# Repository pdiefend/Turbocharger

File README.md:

# Turbocharger
Turbocharger started as a Google Code Project and is in the process of being migrated to GitHub.
Farewell old friend.

The Turbocharger Arduino motor driver is a motor driver designed to amplify the abilities for Arduino robot control. This driver board includes encoder counters, an on-board motor driver, and serial communication headers to be as adaptable as possible for projects needing small motors with encoders.

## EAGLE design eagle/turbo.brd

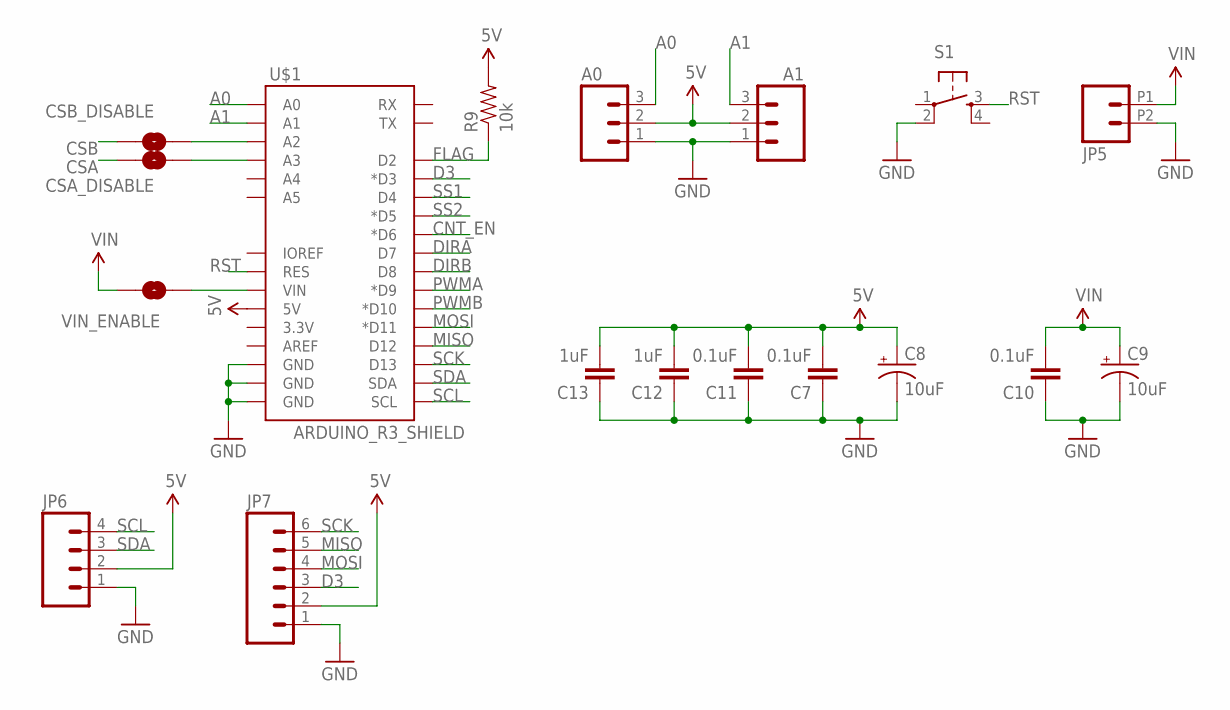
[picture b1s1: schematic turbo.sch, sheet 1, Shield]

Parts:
A0, A1: M03LOCK; 1X03_LOCK
C7, C10, C11: 0.1uF; 0603-CAP
C8, C9: 10uF; PANASONIC_C
C12, C13: 1uF; 0603-CAP
CSA_DISABLE: SOLDERJUMPERTRACE; SJ_2S-TRACE
CSB_DISABLE: SOLDERJUMPERTRACE; SJ_2S-TRACE
JP5: M022.54MM_SCREWTERM; 1X02_2.54_SCREWTERM
JP6: M04POLAR_LOCK; MOLEX-1X4_LOCK
JP7: M06POLAR_LOCK; MOLEX-1X6_LOCK
R9: 10k; 0603-RES
S1: TAC_SWITCHSMD; TACTILE_SWITCH_SMD
U$1: ARDUINO_R3_SHIELD; UNO_R3_SHIELD
VIN_ENABLE: SOLDERJUMPERNO; SJ_2S-NO

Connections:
5V: A0.2, A1.2, C7.2, C8.+, C11.2, C12.2, C13.2, JP6.2, JP7.2, R9.2, U$1.5V; also elsewhere on the board
A0: A0.3, U$1.A0
A1: A1.3, U$1.A1
CNT_EN: U$1.D6 (*D6); also elsewhere on the board
CSA: CSA_DISABLE.2; also elsewhere on the board
CSB: CSB_DISABLE.2; also elsewhere on the board
D3: JP7.3, U$1.D3 (*D3)
DIRA: U$1.D7; also elsewhere on the board
DIRB: U$1.D8; also elsewhere on the board
FLAG: R9.1, U$1.D2; also elsewhere on the board
GND: A0.1, A1.1, C7.1, C8.-, C9.-, C10.1, C11.1, C12.1, C13.1, JP5.P2 (2), JP6.1, JP7.1, S1.2, U$1.GND@0 (GND), U$1.GND@1 (GND), U$1.GND@2 (GND); also elsewhere on the board
MISO: JP7.5, U$1.D12; also elsewhere on the board
MOSI: JP7.4, U$1.D11 (*D11); also elsewhere on the board
unnamed: CSB_DISABLE.1, U$1.A2
unnamed: CSA_DISABLE.1, U$1.A3
unnamed: U$1.VIN, VIN_ENABLE.2
PWMA: U$1.D9 (*D9); also elsewhere on the board
PWMB: U$1.D10 (*D10); also elsewhere on the board
RST: S1.3, U$1.RES
SCK: JP7.6, U$1.D13; also elsewhere on the board
SCL: JP6.4, U$1.SCL
SDA: JP6.3, U$1.SDA
SS1: U$1.D4; also elsewhere on the board
SS2: U$1.D5 (*D5); also elsewhere on the board
VIN: C9.+, C10.2, JP5.P1 (1), VIN_ENABLE.1; also elsewhere on the board

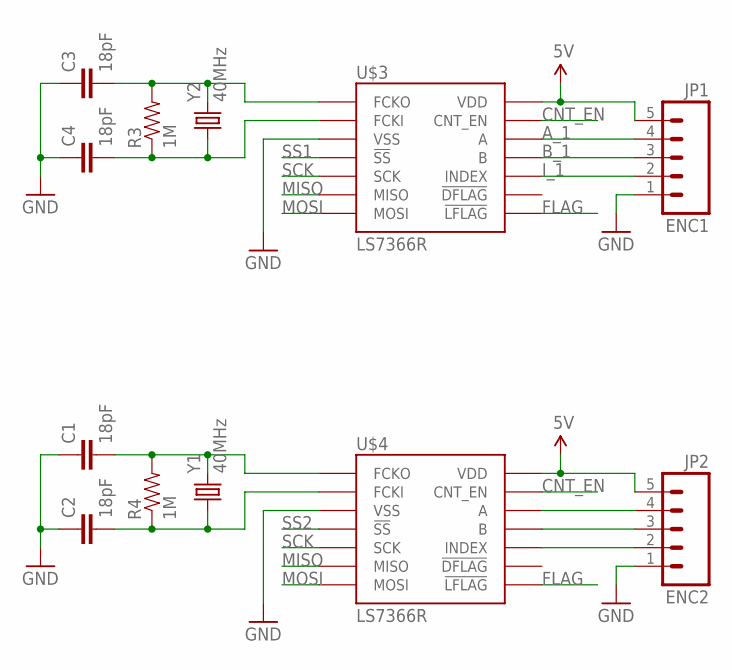
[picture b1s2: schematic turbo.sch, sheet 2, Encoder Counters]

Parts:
C1, C2, C3, C4: 18pF; 0603-CAP
JP1: ENC1; 1X05_LOCK
JP2: ENC2; 1X05_LOCK
R3, R4: 1M; 0603-RES
U$3, U$4: LS7366R; SOIC14
Y1, Y2: 40MHz; CRYSTAL-SMD-5X3

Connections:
5V: JP1.5, JP2.5, U$3.14 (VDD), U$4.14 (VDD); also elsewhere on the board
A_1: JP1.4, U$3.12 (A)
B_1: JP1.3, U$3.11 (B)
CNT_EN: U$3.13 (CNT_EN), U$4.13 (CNT_EN); also elsewhere on the board
FLAG: U$3.8 (!LFLAG), U$4.8 (!LFLAG); also elsewhere on the board
GND: C1.1, C2.1, C3.1, C4.1, JP1.1, JP2.1, U$3.3 (VSS), U$4.3 (VSS); also elsewhere on the board
I_1: JP1.2, U$3.10 (INDEX)
MISO: U$3.6 (MISO), U$4.6 (MISO); also elsewhere on the board
MOSI: U$3.7 (MOSI), U$4.7 (MOSI); also elsewhere on the board
unnamed: C3.2, R3.2, U$3.1 (FCKO), Y2.3 (2)
unnamed: C4.2, R3.1, U$3.2 (FCKI), Y2.1
unnamed: JP2.4, U$4.12 (A)
unnamed: JP2.3, U$4.11 (B)
unnamed: JP2.2, U$4.10 (INDEX)
unnamed: C1.2, R4.2, U$4.1 (FCKO), Y1.3 (2)
unnamed: C2.2, R4.1, U$4.2 (FCKI), Y1.1
SCK: U$3.5 (SCK), U$4.5 (SCK); also elsewhere on the board
SS1: U$3.4 (!SS); also elsewhere on the board
SS2: U$4.4 (!SS); also elsewhere on the board

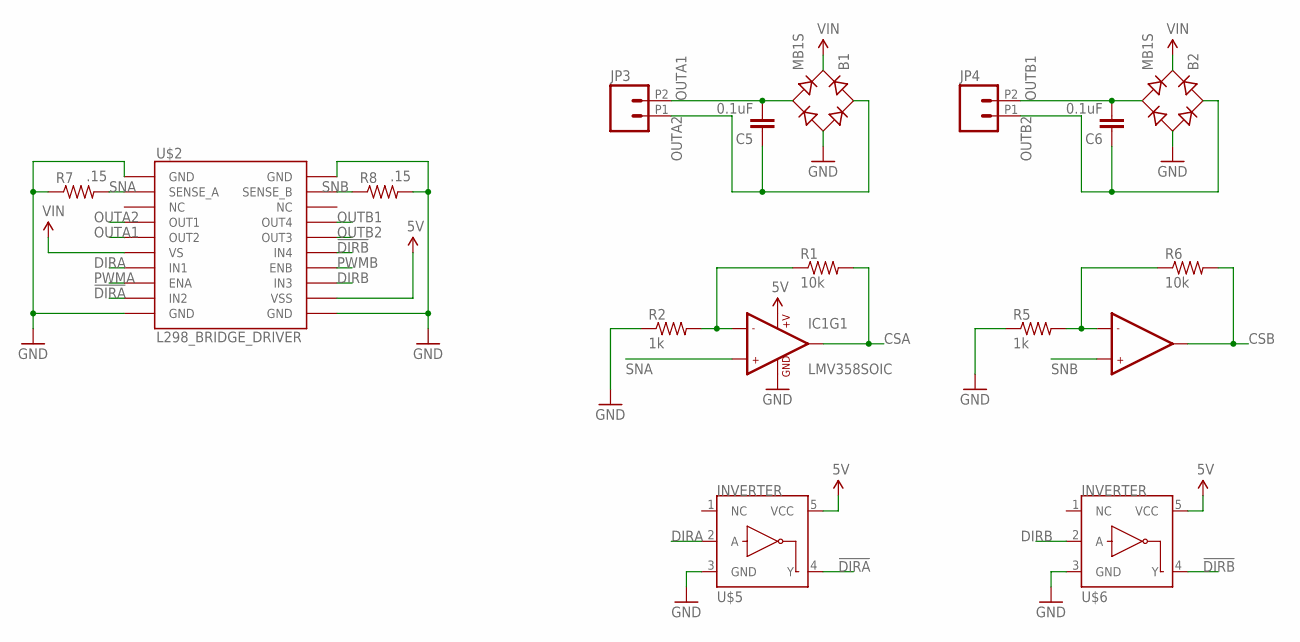
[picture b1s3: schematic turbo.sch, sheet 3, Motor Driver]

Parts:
B1, B2: MB1S; SOIC-4
C5, C6: 0.1uF; 0603-CAP
IC1: LMV358SOIC; SO08
JP3, JP4: M022.54MM_SCREWTERM; 1X02_2.54_SCREWTERM
R1, R6: 10k; 0603-RES
R2, R5: 1k; 0603-RES
R7, R8: .15; 1206
U$2: L298_BRIDGE_DRIVER; POWERSO20
U$5, U$6: INVERTER; SOT23-5

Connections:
5V: IC1.8 (+V), U$2.12 (VSS), U$5.5 (VCC), U$6.5 (VCC); also elsewhere on the board
!DIRA: U$2.9 (IN2), U$5.4 (Y)
!DIRB: U$2.15 (IN4), U$6.4 (Y)
CSA: IC1.1 (OUT1), R1.2; also elsewhere on the board
CSB: IC1.7 (OUT2), R6.2; also elsewhere on the board
DIRA: U$2.7 (IN1), U$5.2 (A); also elsewhere on the board
DIRB: U$2.13 (IN3), U$6.2 (A); also elsewhere on the board
GND: B1.-, B2.-, IC1.4 (GND), R2.1, R5.1, R7.1, R8.2, U$2.1 (GND), U$2.10 (GND), U$2.11 (GND), U$2.20 (GND), U$2.P$1 (GND), U$5.3 (GND), U$6.3 (GND); also elsewhere on the board
unnamed: IC1.6 (-IN2), R5.2, R6.1
unnamed: IC1.2 (-IN1), R1.1, R2.2
OUTA1: B1.~2 (AC2), C5.2, JP3.P2 (2), U$2.5 (OUT2)
OUTA2: B1.~1 (AC1), C5.1, JP3.P1 (1), U$2.4 (OUT1)
OUTB1: B2.~2 (AC2), C6.2, JP4.P2 (2), U$2.17 (OUT4)
OUTB2: B2.~1 (AC1), C6.1, JP4.P1 (1), U$2.16 (OUT3)
PWMA: U$2.8 (ENA); also elsewhere on the board
PWMB: U$2.14 (ENB); also elsewhere on the board
SNA: IC1.3 (+IN1), R7.2, U$2.2 (SENSE_A)
SNB: IC1.5 (+IN2), R8.1, U$2.19 (SENSE_B)
VIN: B1.+, B2.+, U$2.6 (VS); also elsewhere on the board

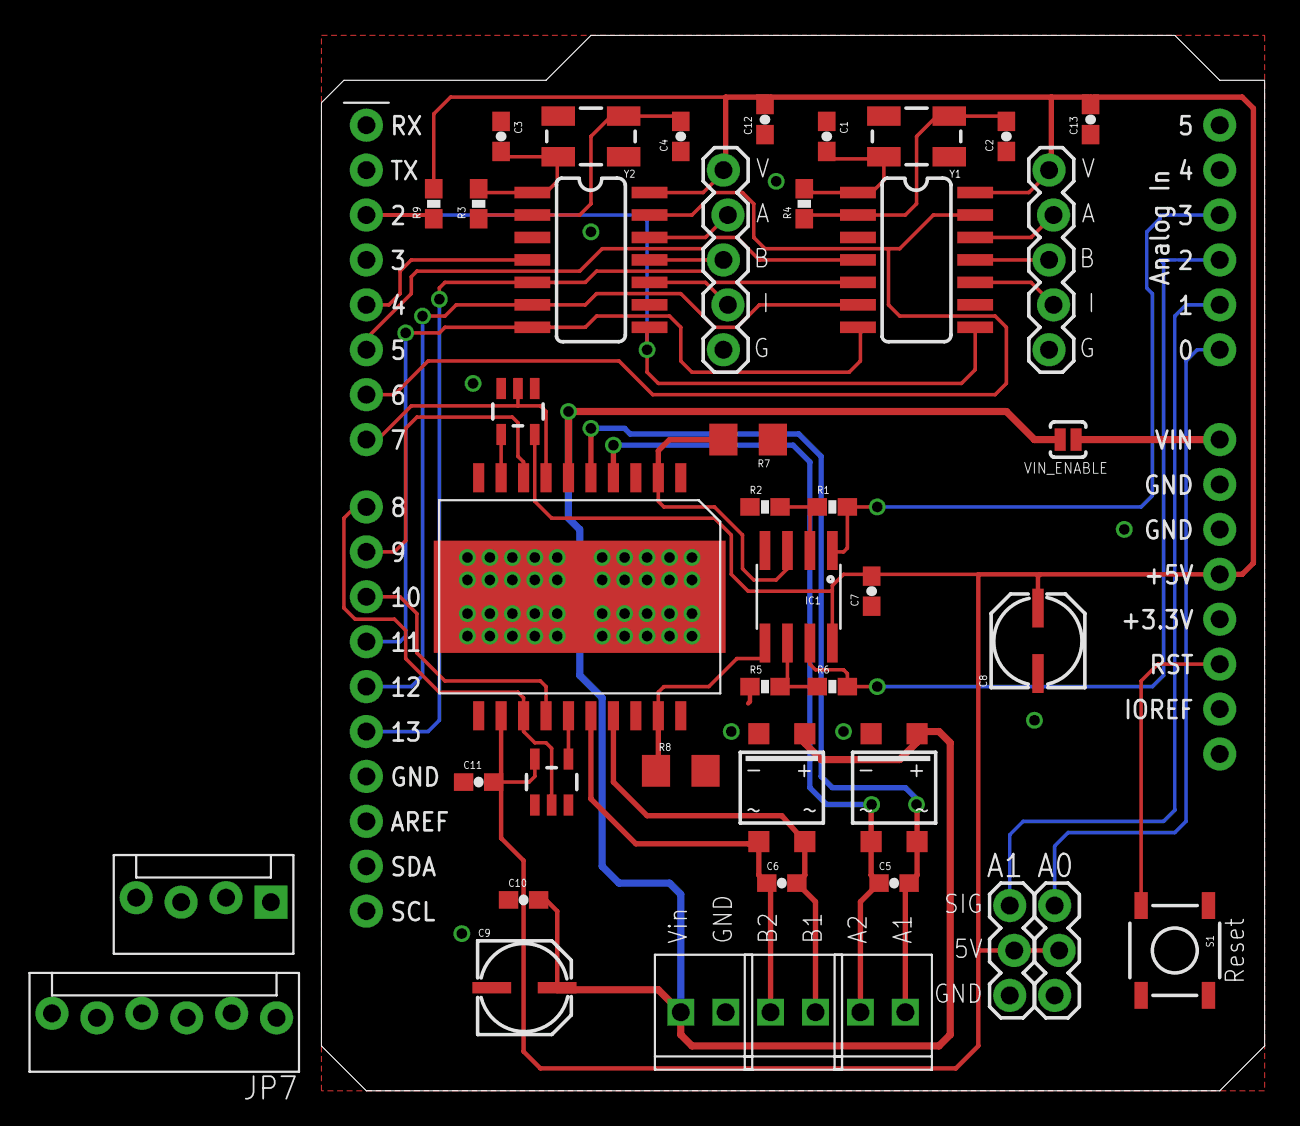
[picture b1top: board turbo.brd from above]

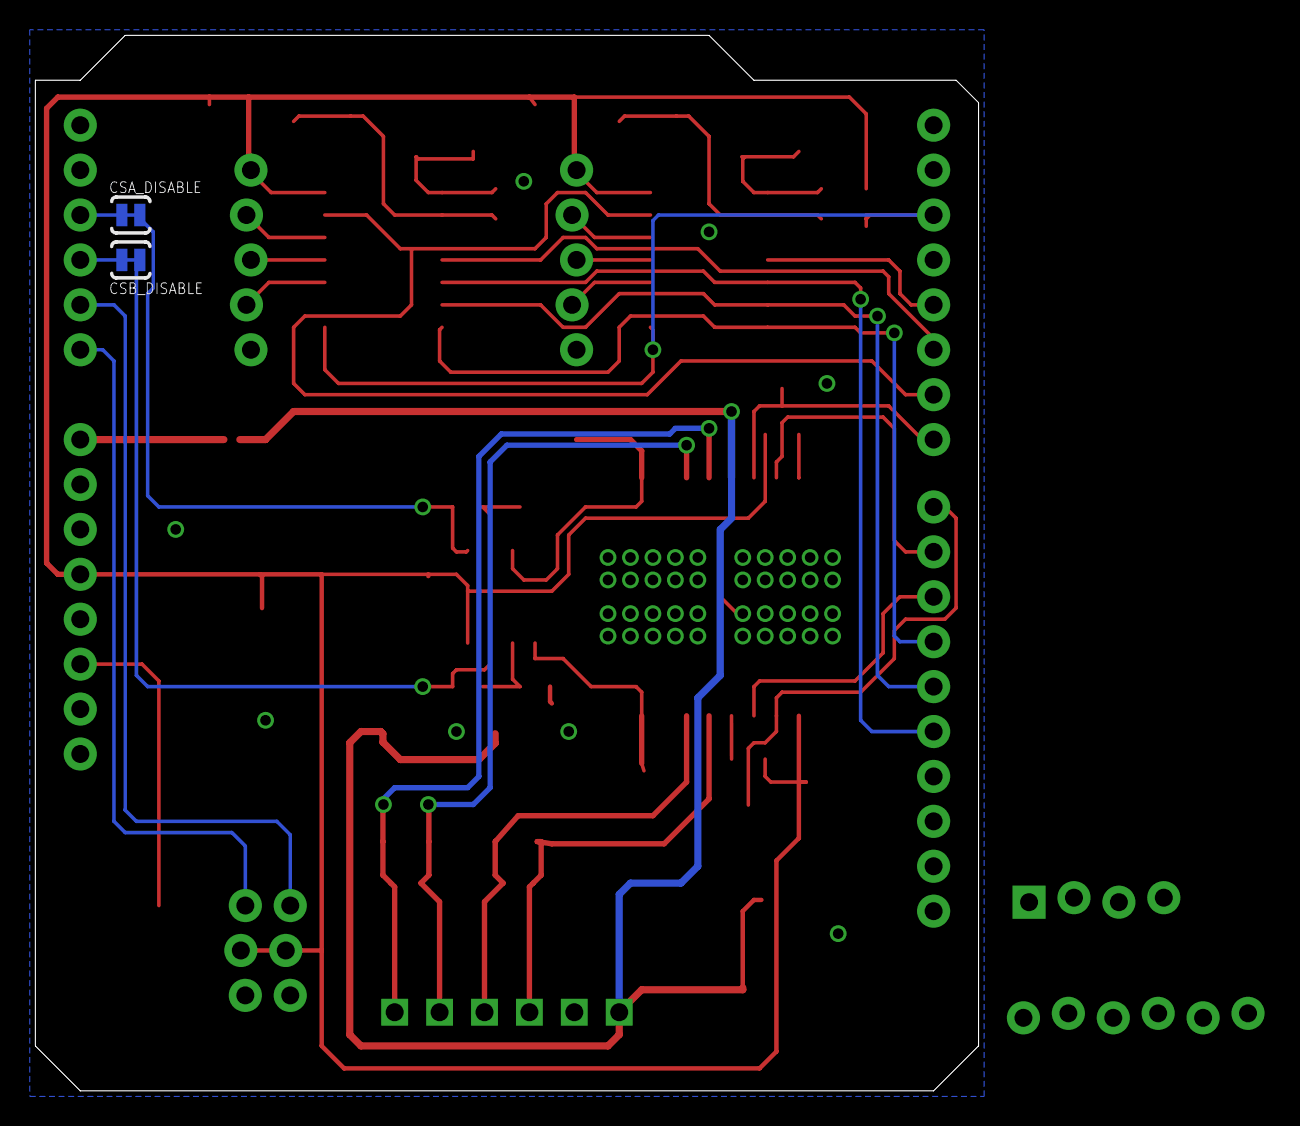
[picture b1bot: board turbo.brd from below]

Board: 2 copper layers, 53.3 x 59.7 mm, 46 parts (2 on the bottom side), 45 nets.

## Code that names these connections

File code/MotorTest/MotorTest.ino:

#define DIRA 7
#define DIRB 8
#define PWMA 9
#define PWMB 10
#define CSA A3
#define CSB A2

void setup(){
  Serial.begin(115200);

  pinMode(DIRA, OUTPUT);
  pinMode(DIRB, OUTPUT);
  pinMode(PWMA, OUTPUT);
  pinMode(PWMB, OUTPUT);

  digitalWrite(DIRA, LOW);
  digitalWrite(DIRB, LOW);
  digitalWrite(PWMA, LOW);
  digitalWrite(PWMB, LOW);

  pinMode(A3, INPUT);
  pinMode(A4, INPUT);

  Serial.println("Begin in 1s");
  delay(1000);
}

void loop(){
  digitalWrite(DIRA, HIGH);
  Serial.println("Forward Ramp Up");
  for(int i = 0; i < 255; i++){
    analogWrite(PWMA, i);
    delay(10); 
  }

  Serial.println("Forward Hold");
  analogWrite(PWMA, 255);
  delay(1000);
  Serial.println(analogRead(CSA));
  delay(1000);

  Serial.println("Forward Ramp Down");
  for(int i = 255; i > 0; i--){
    analogWrite(PWMA, i);
    delay(10); 
  }

  digitalWrite(PWMA, LOW);
  Serial.println("Halt");
  delay(2000);  



  digitalWrite(DIRA, LOW);
  Serial.println("Backward Ramp Up");
  for(int i = 0; i < 255; i++){
    analogWrite(PWMA, i);
    delay(10); 
  }

  Serial.println("Backward Hold");
  analogWrite(PWMA, 255);
  delay(1000);
  Serial.println(analogRead(CSA));
  delay(1000);

  Serial.println("Backward Ramp Down");
  for(int i = 255; i > 0; i--){
    analogWrite(PWMA, i);
    delay(10); 
  }

  digitalWrite(PWMA, LOW);
  Serial.println("Halt");
  delay(2000);  
}

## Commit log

2015-03-16 First Actual Commit of Files
    Files being migrated from the Google Code Repository that is being
    broken up into different projects with different owners.

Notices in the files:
parts and their libraries:
SparkFun-Boards: Licensing: Creative Commons ShareAlike 4.0 International - https://creativecommons.org/licenses/by-sa/4.0
